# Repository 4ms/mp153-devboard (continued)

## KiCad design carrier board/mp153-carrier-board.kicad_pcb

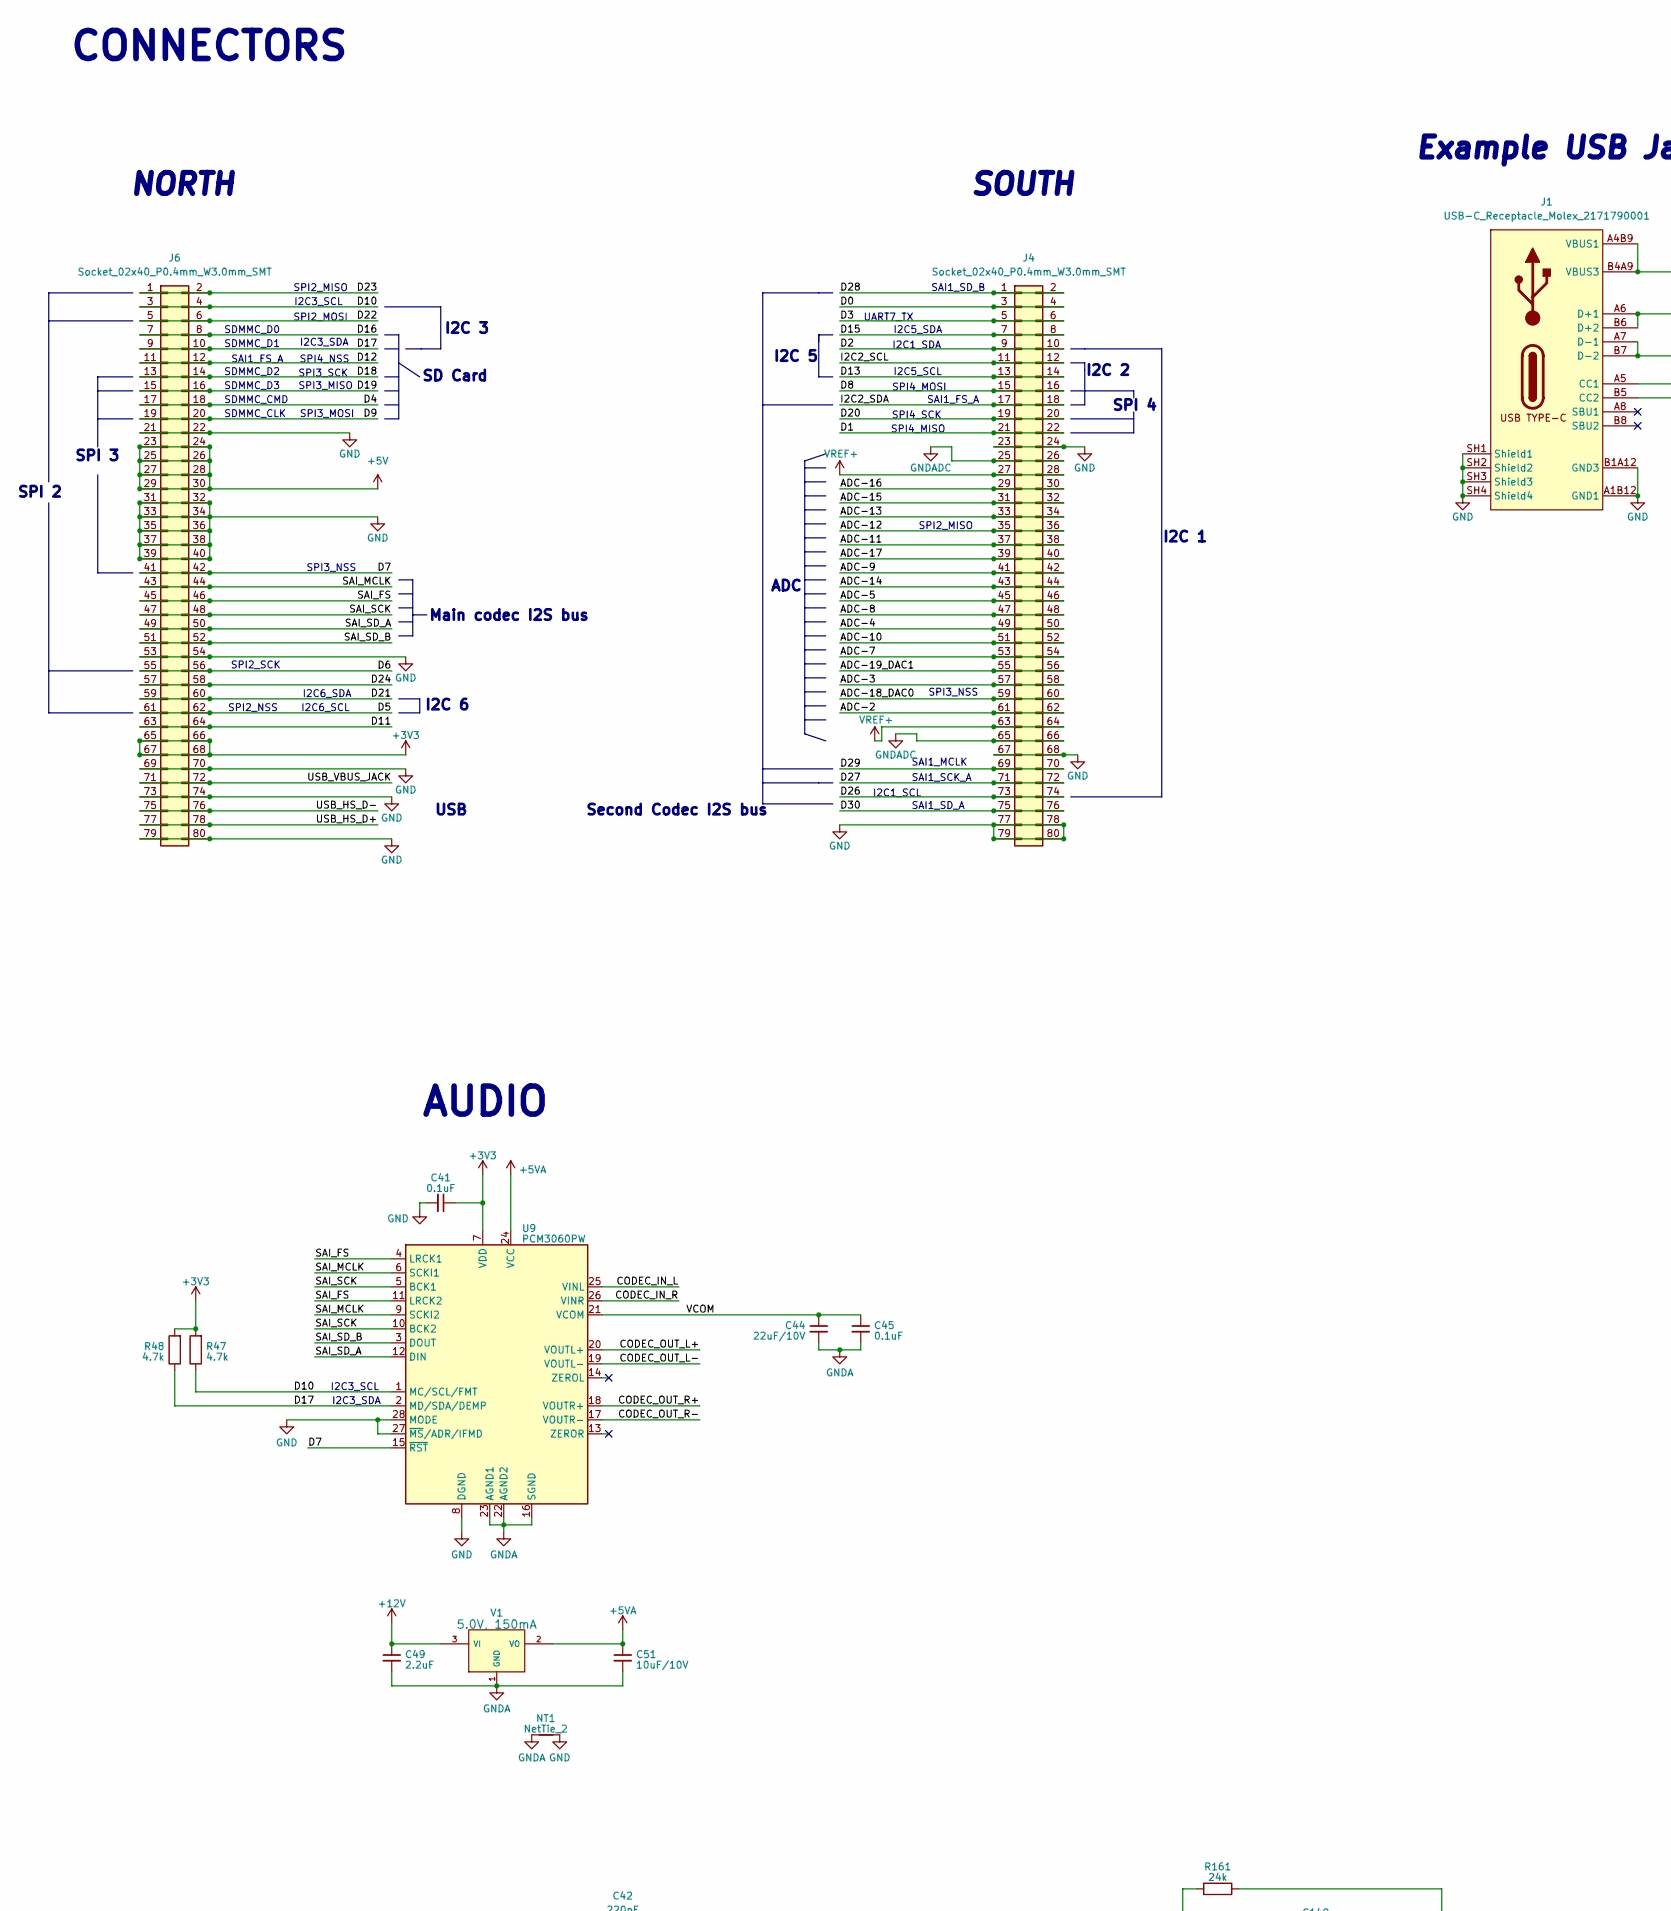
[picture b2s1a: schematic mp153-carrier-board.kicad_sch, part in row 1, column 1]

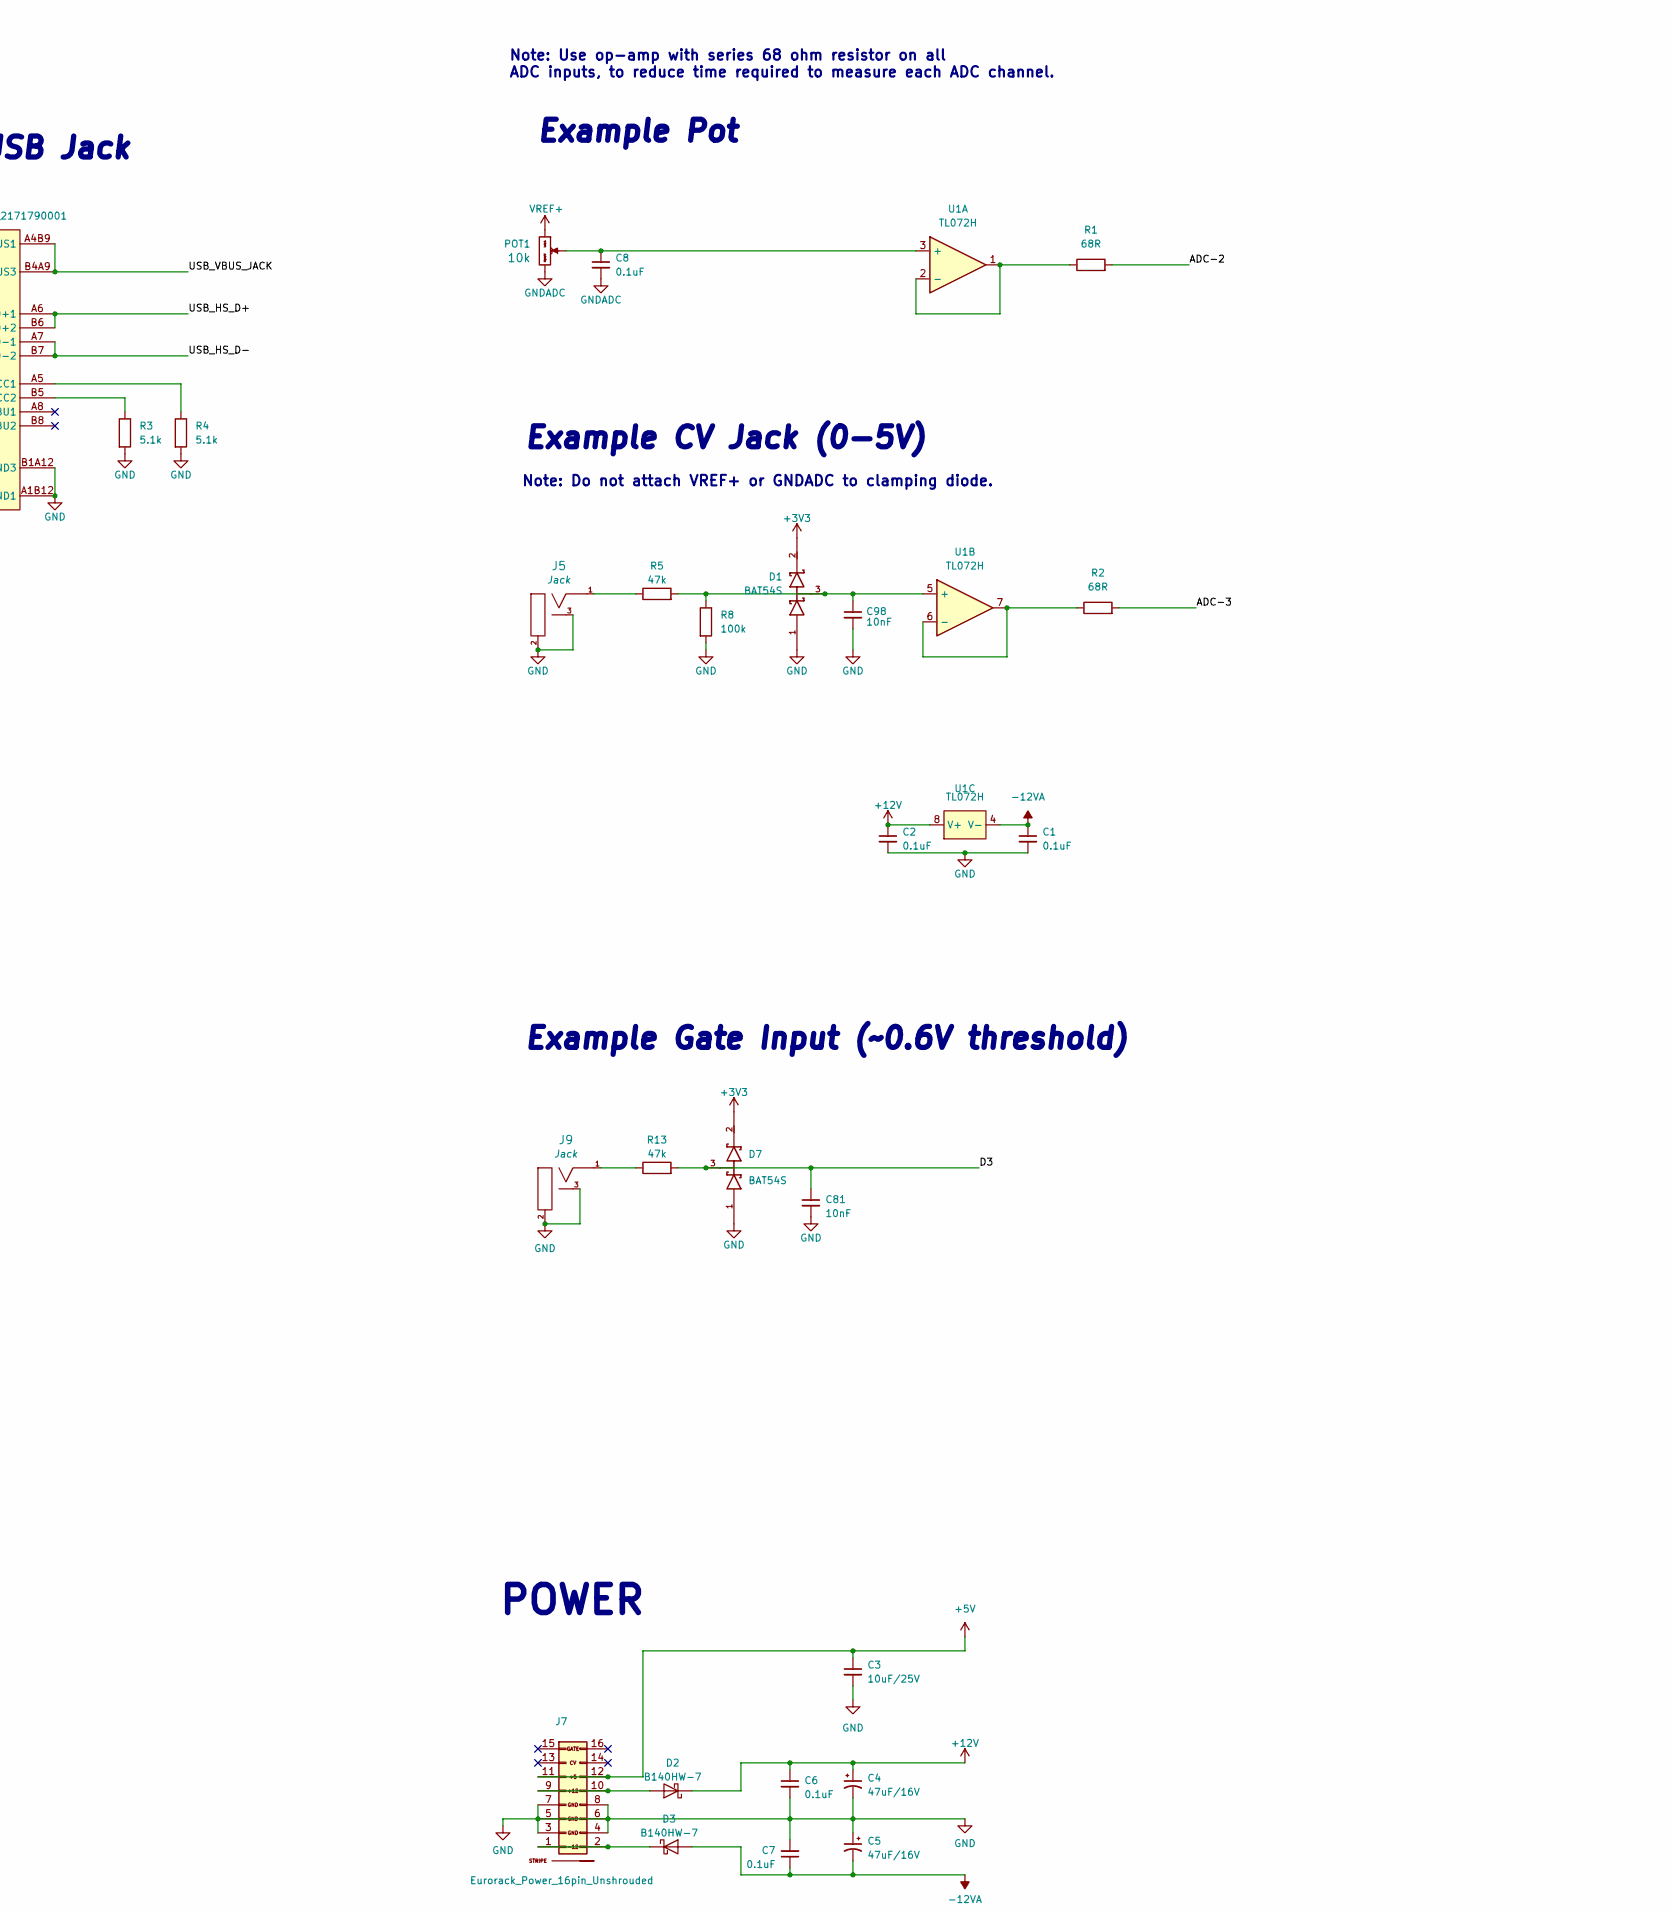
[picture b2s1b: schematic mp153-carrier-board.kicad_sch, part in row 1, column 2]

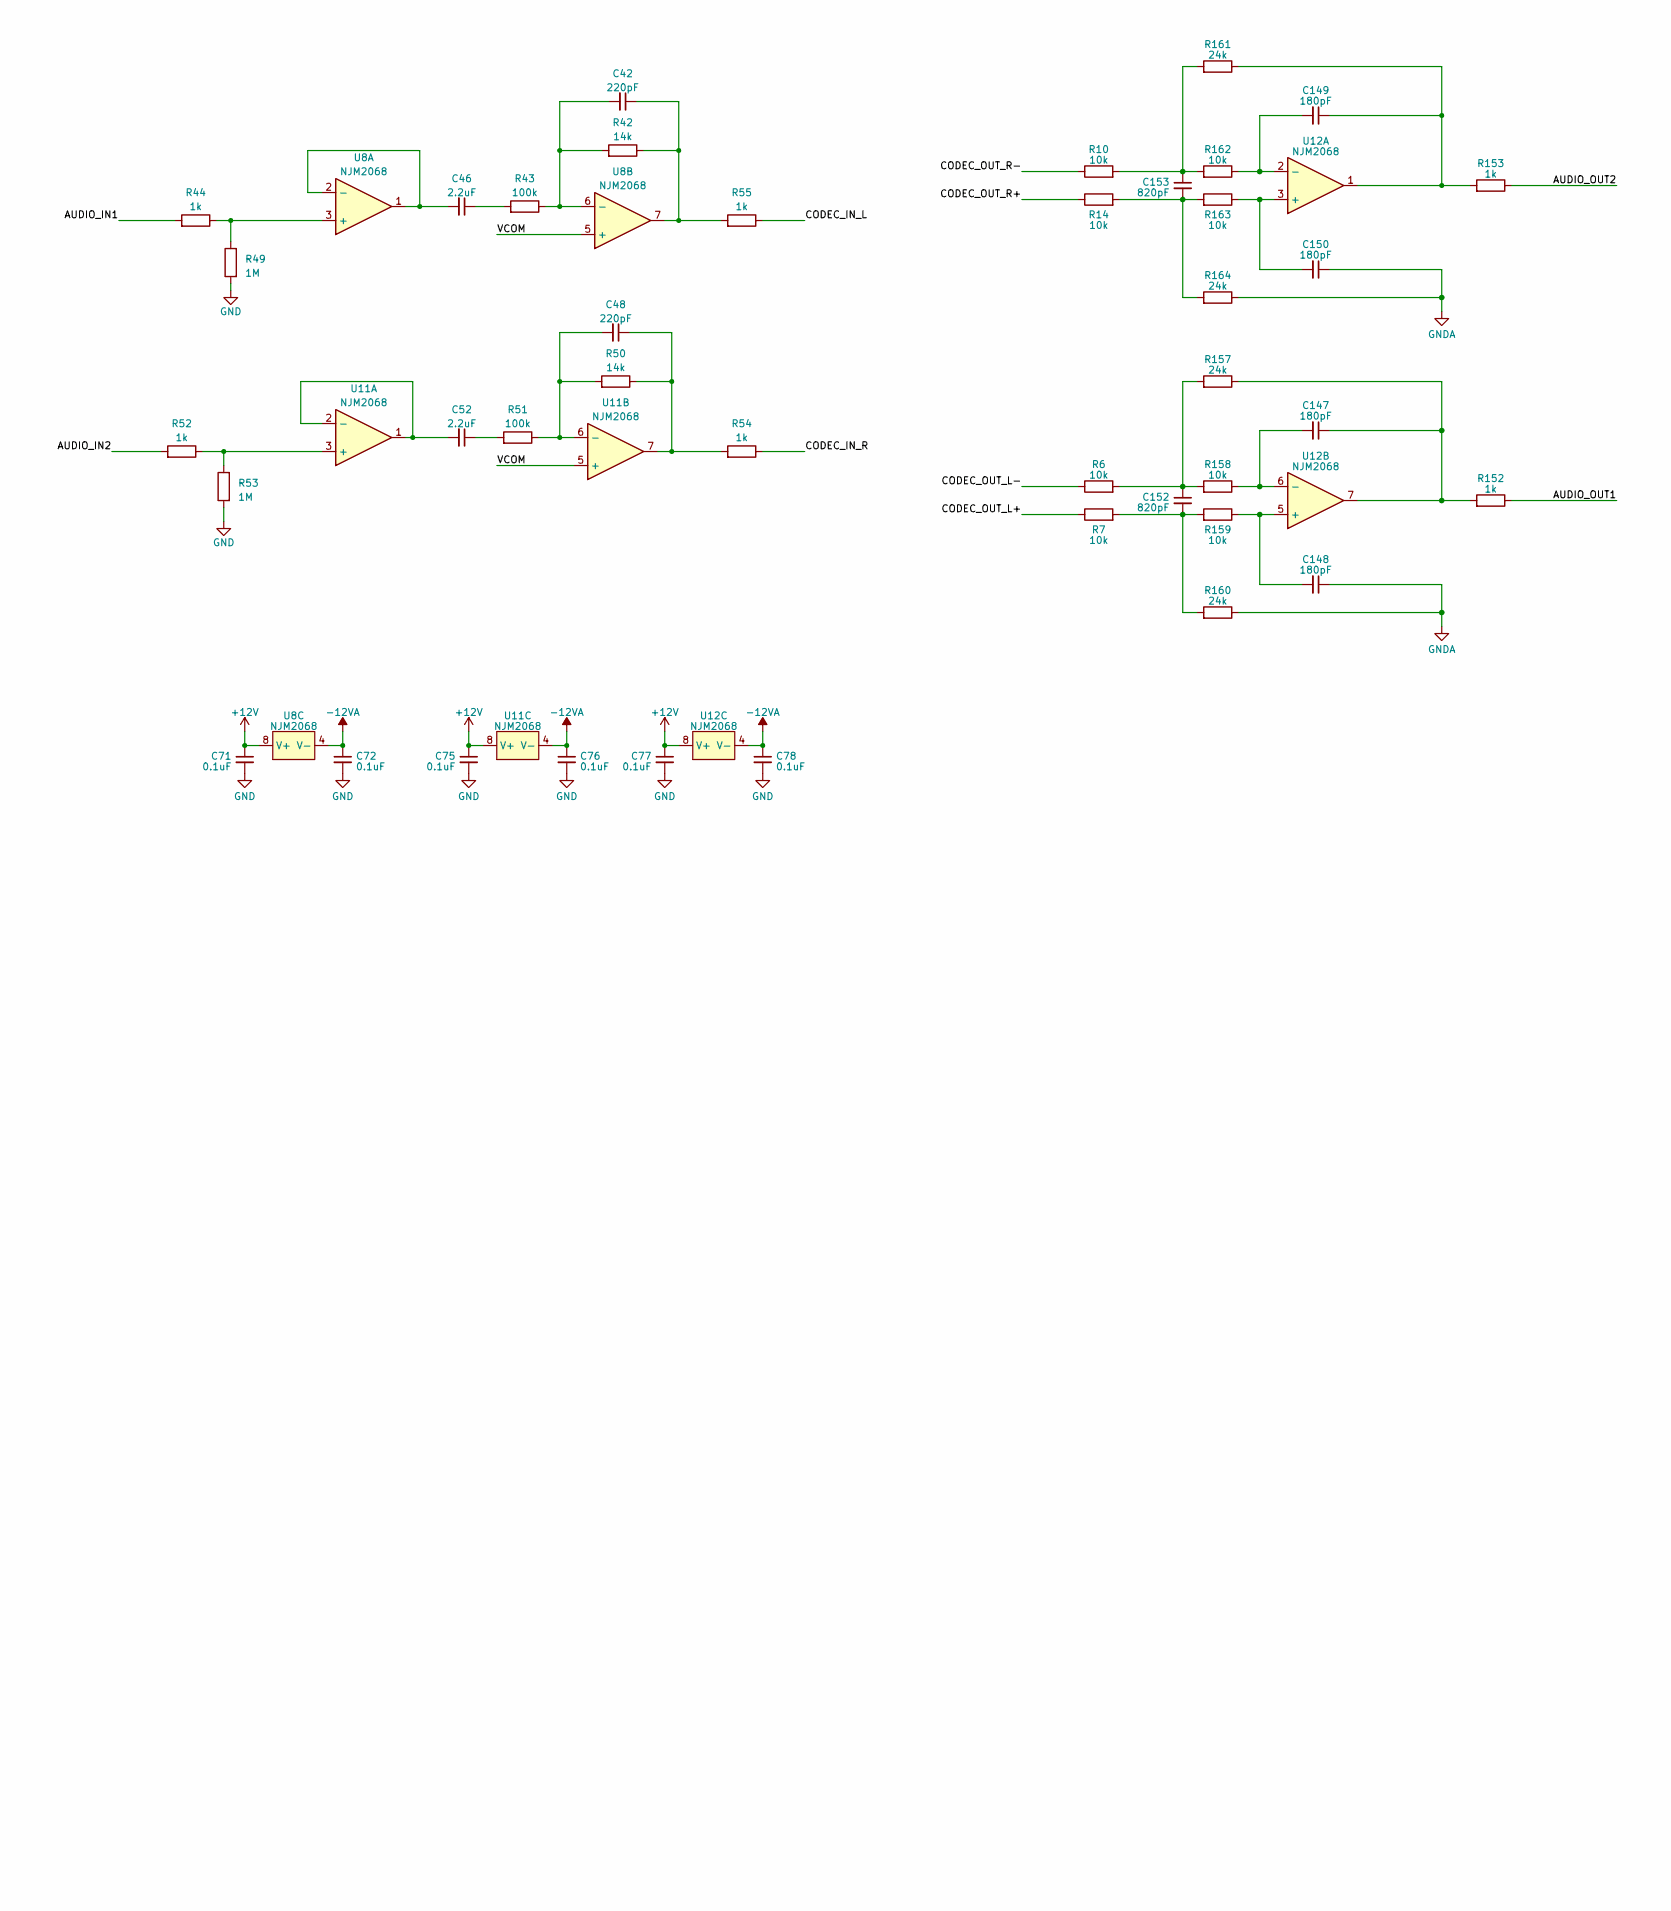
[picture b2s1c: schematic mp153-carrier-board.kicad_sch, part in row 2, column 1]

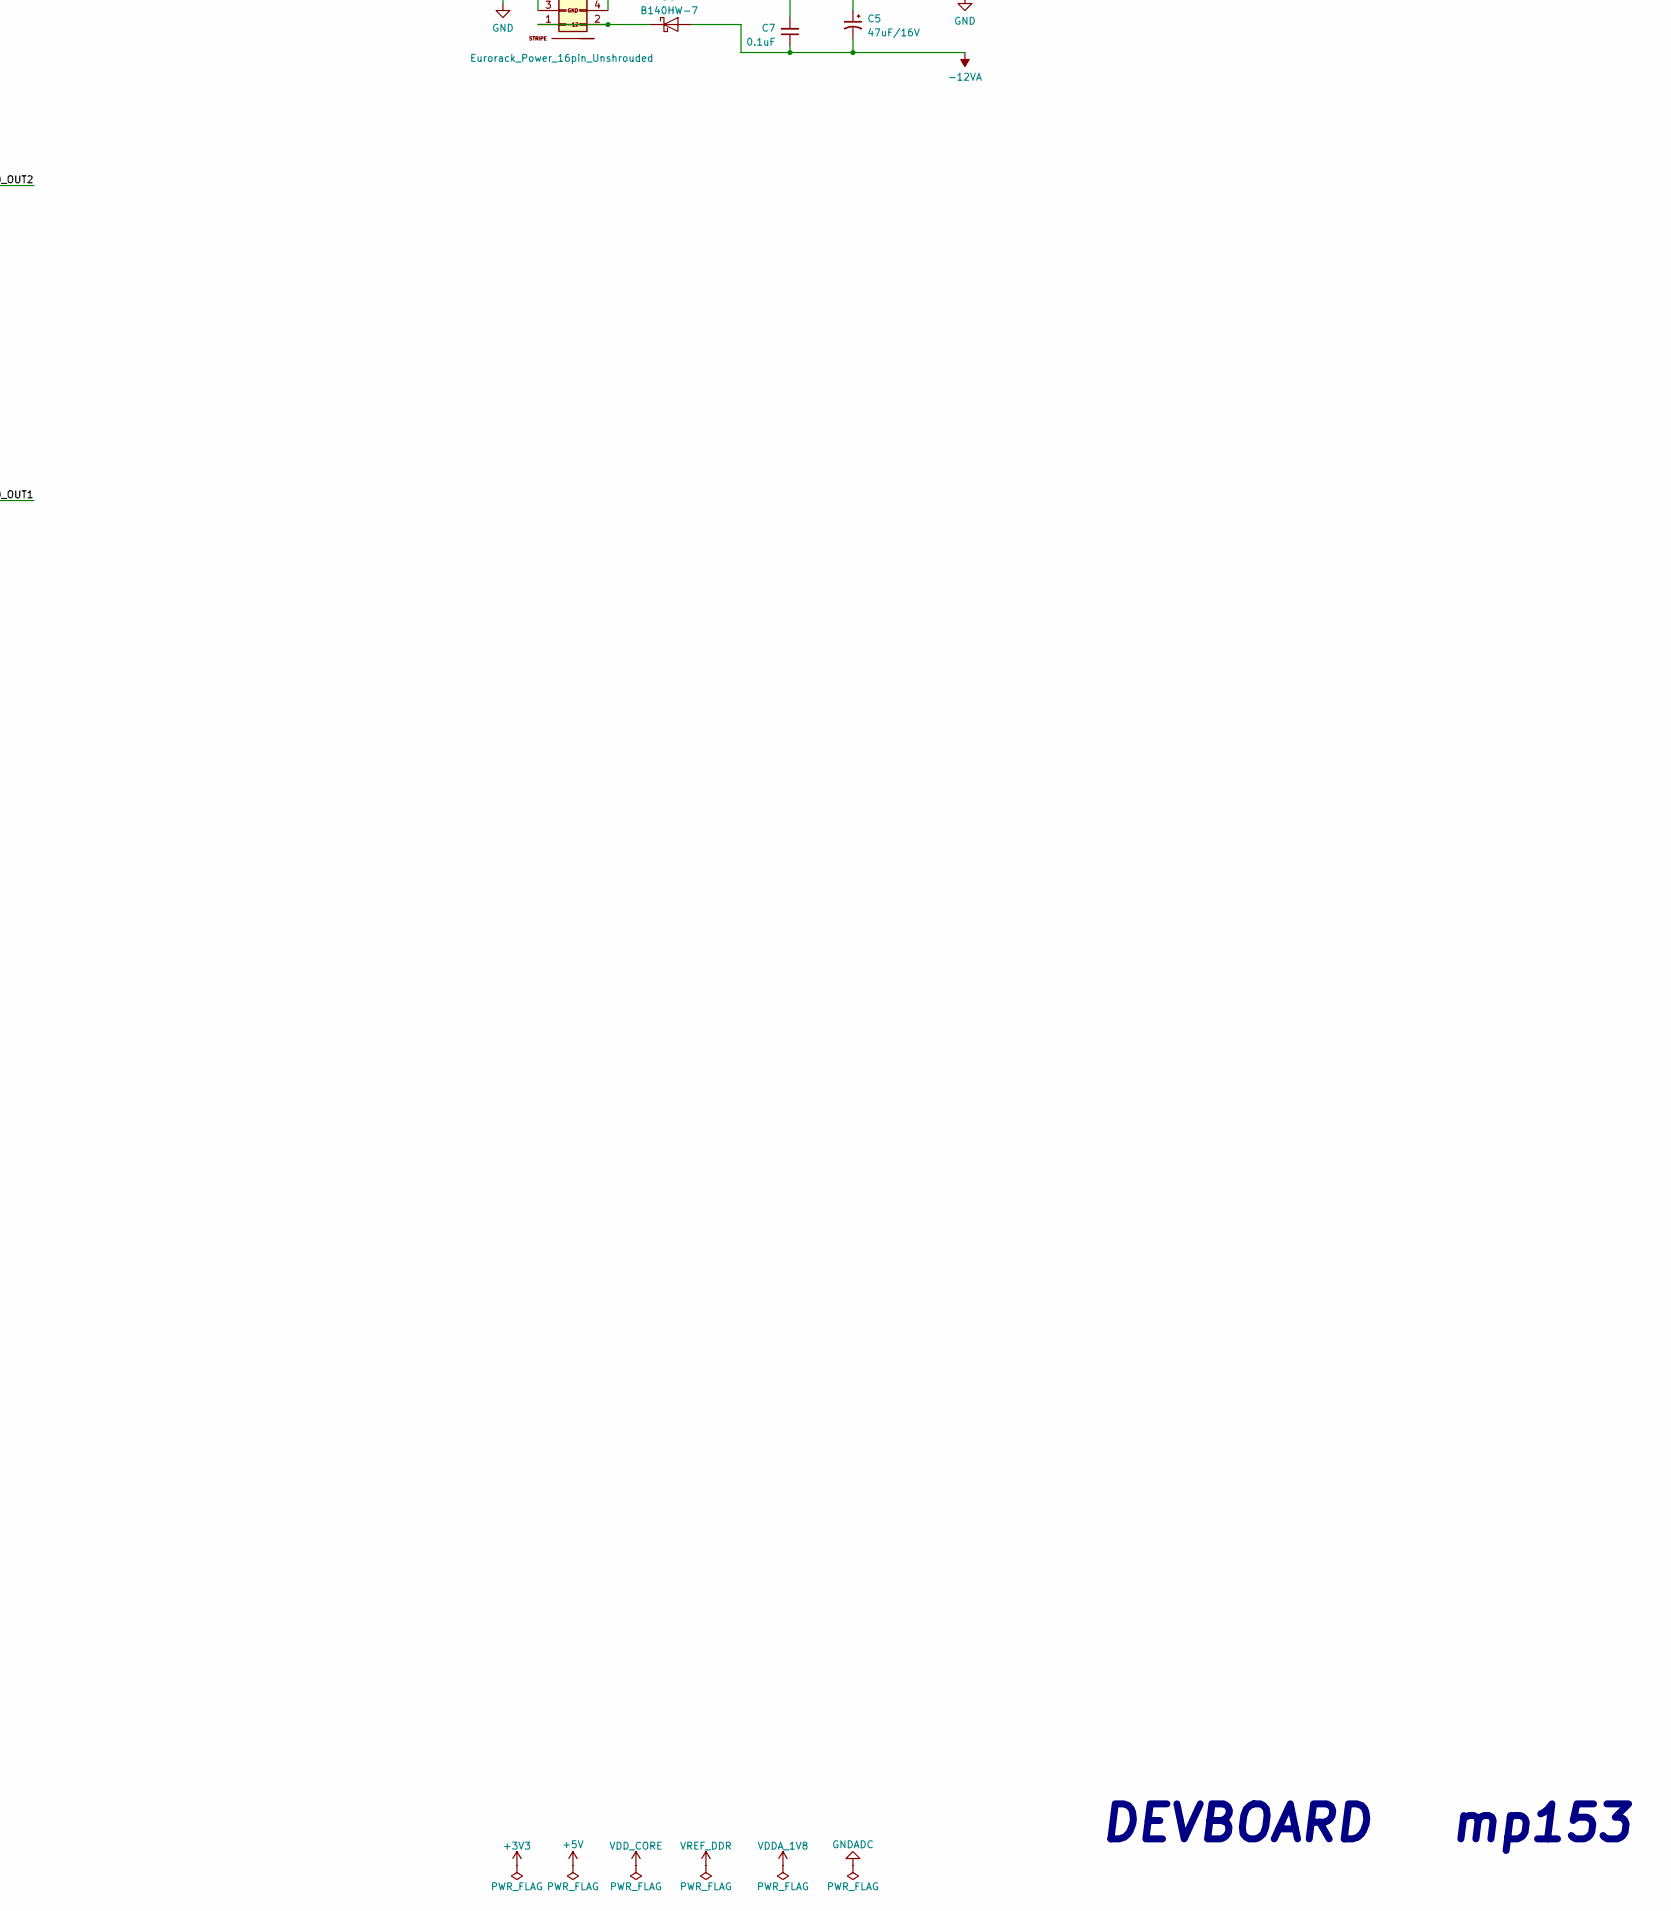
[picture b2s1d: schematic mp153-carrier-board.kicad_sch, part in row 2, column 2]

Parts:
C1, C2, C8: 100nF_0603_16V; C_0603; Part Number 0603YC104KAT2A; JLCPCB ID C14663
C3: 10uF_0805_25V; C_0805; Part Number GRM21BR61E106MA73L; JLCPCB ID C15850
C4, C5: 47uF_5x5.3_16V; CP_Elec_5x5.3; Part Number VES470M1CTR-0505; JLCPCB ID C134798
C6, C7, C41: 100nF_0402_16V; C_0402; Part Number GCM155R71C104KA55D; JLCPCB ID C1525
C42, C48: 220pF_0603_25V; C_0603; Part Number CC0603JRNPO9BN221; JLCPCB ID C1603
C44: 22uF_0805_10V; C_0805; Part Number LMK212BBJ226MG-T; JLCPCB ID C45783
C45: 0.1uF_0603_16V; C_0603; Part Number 0603YC104KAT2A; JLCPCB ID C14663
C46, C49, C52: 2.2uF_0603_25V; C_0603; Part Number GRM188R6YA225KA12D; JLCPCB ID C57895
C51: 10uF_0603_10V; C_0603; Part Number GRM188R61A106KE69D; JLCPCB ID C19702
C71, C72, C75, C76, C77, C78: 100nF_0402_50V; C_0402; Part Number GRM155R71H104KE14D; JLCPCB ID C307331
C81, C98: 10nF_0402_16V; C_0402; Part Number CC0402KRX7R7BB103; JLCPCB ID C15195
C147, C148, C149, C150: 180pF_0402_25V; C_0402; Part Number GRM1555C2A181JE01D; JLCPCB ID C106999
C152, C153: 820pF_0402_10v; C_0402; Part Number 0402ZC821KAT2A; JLCPCB ID C565563
D1, D7: BAT54S; SOT23-3_PO132; Part Number BAT54S-7-F; JLCPCB ID C83574
D2, D3: B140HW-7; D_SOD-123; Part Number B140HW-7; JLCPCB ID C134429
J1: USB-C_Receptacle_Molex_2171790001; USB_C_Receptacle_Molex_2171790001; Part Number 217179-0001; JLCPCB ID C2894899
J4, J6: Socket_02x40_P0.4mm_W3.0mm_SMT; Connector-80socket-P0.4mm-W3.0mm; Part Number DF40HC(3.0)-80DS-0.4V(51); JLCPCB ID C2858577
J5, J9: 3.5mm_Mono_Switched_sm; EighthInch_PJ398SM; Part Number WQP-WQP518MA
J7: Eurorack_Power_16pin_Unshrouded; Pins_2x08_2.54mm_TH_EurorackPower; Part Number 1-1602FBV0T
NT1: NetTie_2; NetTie-2_SMD_Pad0.5mm
POT1: 16mm_CtrDet_10k; Pot_16mm_CtrDet_RV16AF-4A; Part Number RV16AF-4A-15FW-B10k-3C
R1, R2: 68R_0603; R_0603; Part Number RC0603FR-0768RL; JLCPCB ID C27592
R3, R4: 5.1k_0603; R_0603; Part Number RC0603FR-075K1L; JLCPCB ID C105580
R5, R13: 47k_0402; R_0402; Part Number RC0402FR-0747KL; JLCPCB ID C93943
R6, R7, R10, R14, R158, R159, R162, R163: 10k_0402; R_0402; Part Number RC0402FR-0710KL; JLCPCB ID C60490
R8: 100k_0603; R_0603; Part Number RC0603FR-07100KL; JLCPCB ID C14675
R42, R50: 14k_0402; R_0402; Part Number RC0402FR-0714KL; JLCPCB ID C327372
R43, R51: 100k_0402; R_0402; Part Number RC0402FR-07100KL; JLCPCB ID C60491
R44, R52, R54, R55, R152, R153: 1k_0402; R_0402; Part Number RC0402FR-071KL; JLCPCB ID C106235
R47, R48: 4.7k_0402; R_0402; Part Number RC0402FR-074K7L; JLCPCB ID C105871
R49, R53: 1M_0402; R_0402; Part Number RC0402FR-071ML; JLCPCB ID C138033
R157, R160, R161, R164: 24k_0402; R_0402; Part Number RC0402FR-0724KL; JLCPCB ID C138026
U1: TL072H; TSSOP-8_4.4x3mm_Pitch0.65mm; Part Number TL072HIPWR; JLCPCB ID C4370341
U8, U11, U12: NJM2068; TSSOP-8_4.4x3mm_Pitch0.65mm; Part Number NJM2068V-TE1
U9: PCM3060PW; TSSOP-28_4.4x9.7mm_P0.65mm; Part Number PCM3060PW
V1: AP2120N-5.0TRG1; SOT23-3_PO132; Part Number AP2120N-5.0TRG1

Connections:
+3V3: C41.1, D1.2 (cathode), D7.2 (cathode), J6.65, J6.66, J6.67, J6.68, R47.2, R48.2, U9.7 (VDD)
+5V: C3.1, J6.23, J6.24, J6.25, J6.26, J6.27, J6.28, J6.29, J6.30, J7.11 (5V), J7.12 (5V)
+5VA: C51.1, U9.24 (VCC), V1.2 (VO)
+12V: C2.1, C4.1, C6.1, C49.1, C71.1, C75.1, C77.1, D2.1 (K), U1.8 (V+), U8.8 (V+), U11.8 (V+), U12.8 (V+), V1.3 (VI)
-12VA: C1.1, C5.2, C7.1, C72.1, C76.1, C78.1, D3.2 (A), U1.4 (V-), U8.4 (V-), U11.4 (V-), U12.4 (V-)
/ADC-2: J4.61, J4.62, R1.2
/ADC-3: J4.57, J4.58, R2.2
/ADC-4: J4.49, J4.50
/ADC-5: J4.45, J4.46
/ADC-7: J4.53, J4.54
/ADC-8: J4.47, J4.48
/ADC-9: J4.41, J4.42
/ADC-10: J4.51, J4.52
/ADC-11: J4.37, J4.38
/ADC-12: J4.35, J4.36
/ADC-13: J4.33, J4.34
/ADC-14: J4.43, J4.44
/ADC-15: J4.31, J4.32
/ADC-16: J4.29, J4.30
/ADC-17: J4.39, J4.40
/ADC-18_DAC0: J4.59, J4.60
/ADC-19_DAC1: J4.55, J4.56
/AUDIO_IN1: R44.2
/AUDIO_IN2: R52.2
/AUDIO_OUT1: R152.1
/AUDIO_OUT2: R153.1
/CODEC_IN_L: R55.1, U9.25 (VINL)
/CODEC_IN_R: R54.1, U9.26 (VINR)
/CODEC_OUT_L+: R7.1, U9.20 (VOUTL+)
/CODEC_OUT_L-: R6.1, U9.19 (VOUTL-)
/CODEC_OUT_R+: R14.1, U9.18 (VOUTR+)
/CODEC_OUT_R-: R10.1, U9.17 (VOUTR-)
/D0: J4.3, J4.4
/D1: J4.21, J4.22
/D2: J4.9, J4.10
/D3: C81.1, D7.3 (AK), J4.5, J4.6, R13.2
/D4: J6.17, J6.18
/D5: J6.61, J6.62
/D6: J6.55, J6.56
/D7: J6.41, J6.42, U9.15 (~RST)
/D8: J4.15, J4.16
/D9: J6.19, J6.20
/D10: J6.3, J6.4, R47.1, U9.1 (MC/SCL/FMT)
/D11: J6.63, J6.64
/D12: J6.11, J6.12
/D13: J4.13, J4.14
/D15: J4.7, J4.8
/D16: J6.7, J6.8
/D17: J6.9, J6.10, R48.1, U9.2 (MD/SDA/DEMP)
/D18: J6.13, J6.14
/D19: J6.15, J6.16
/D20: J4.19, J4.20
/D21: J6.59, J6.60
/D22: J6.5, J6.6
/D23: J6.1, J6.2
/D24: J6.57, J6.58
/D26: J4.73, J4.74
/D27: J4.71, J4.72
/D28: J4.1, J4.2
/D29: J4.69, J4.70
/D30: J4.75, J4.76
/I2C2_SCL: J4.11, J4.12
/I2C2_SDA: J4.17, J4.18
/SAI_FS: J6.45, J6.46, U9.4 (LRCK1), U9.11 (LRCK2)
/SAI_MCLK: J6.43, J6.44, U9.6 (SCKI1), U9.9 (SCKI2)
/SAI_SCK: J6.47, J6.48, U9.5 (BCK1), U9.10 (BCK2)
/SAI_SD_A: J6.49, J6.50, U9.12 (DIN)
/SAI_SD_B: J6.51, J6.52, U9.3 (DOUT)
/USB_HS_D+: J1.A6 (D+1), J1.B6 (D+2), J6.77, J6.78
/USB_HS_D-: J1.A7 (D-1), J1.B7 (D-2), J6.75, J6.76
/USB_VBUS_JACK: J1.A4B9 (VBUS1), J1.B4A9 (VBUS3), J6.71, J6.72
/VCOM: C44.1, C45.1, U8.5 (+), U9.21 (VCOM), U11.5 (+)
GND: C1.2, C2.2, C3.2, C4.2, C5.1, C6.2, C7.2, C41.2, C71.2, C72.2, C75.2, C76.2, C77.2, C78.2, C81.2, C98.2, D1.1 (Anode), D7.1 (Anode), J1.A1B12 (GND1), J1.B1A12 (GND3), J1.SH1 (Shield1), J1.SH2 (Shield2), J1.SH3 (Shield3), J1.SH4 (Shield4), J4.23, J4.24, J4.67, J4.68, J4.77, J4.78, J4.79, J4.80, J5.2 (SHEILD), J5.3 (SW), J6.21, J6.22, J6.31, J6.32, J6.33, J6.34, J6.35, J6.36, J6.37, J6.38, J6.39, J6.40, J6.53, J6.54, J6.69, J6.70, J6.73, J6.74, J6.79, J6.80, J7.3 (GND), J7.4 (GND), J7.5 (GND), J7.6 (GND), J7.7 (GND), J7.8 (GND), J9.2 (SHEILD), J9.3 (SW), NT1.2, R3.2, R4.2, R8.2, R49.2, R53.2, U9.8 (DGND), U9.27 (~MS/ADR/IFMD), U9.28 (MODE)
GNDA: C44.2, C45.2, C49.2, C51.2, C148.1, C150.1, NT1.1, R160.1, R164.1, U9.16 (SGND), U9.22 (AGND2), U9.23 (AGND1), V1.1 (GND)
GNDADC: C8.2, J4.25, J4.26, J4.65, J4.66, POT1.3 (Right)
unnamed: C42.1, R42.1, R55.2, U8.7
unnamed: C46.1, R43.2
unnamed: C48.1, R50.1, R54.2, U11.7
unnamed: C52.1, R51.2
unnamed: C147.1, R152.2, R157.1, U12.7
unnamed: C149.1, R153.2, R161.1, U12.1
unnamed: C152.1, R6.2, R157.2, R158.2
unnamed: C152.2, R7.2, R159.2, R160.2
unnamed: C153.1, R10.2, R161.2, R162.2
unnamed: C153.2, R14.2, R163.2, R164.2
unnamed: C98.1, D1.3 (AK), R5.2, R8.1, U1.5 (+)
unnamed: D2.2 (A), J7.9 (+12V), J7.10 (+12V)
unnamed: D3.1 (K), J7.1 (-12V), J7.2 (-12V)
unnamed: J1.A5 (CC1), R4.1
unnamed: J1.B5 (CC2), R3.1
unnamed: J5.1 (SIG), R5.1
unnamed: J9.1 (SIG), R13.1
unnamed: C8.1, POT1.2 (Center), U1.3 (+)
unnamed: R1.1, U1.1, U1.2 (-)
unnamed: R2.1, U1.6 (-), U1.7
unnamed: R44.1, R49.1, U8.3 (+)
unnamed: C46.2, U8.1, U8.2 (-)
unnamed: C42.2, R42.2, R43.1, U8.6 (-)
unnamed: R52.1, R53.1, U11.3 (+)
unnamed: C52.2, U11.1, U11.2 (-)
unnamed: C48.2, R50.2, R51.1, U11.6 (-)
unnamed: C150.2, R163.1, U12.3 (+)
unnamed: C149.2, R162.1, U12.2 (-)
unnamed: C148.2, R159.1, U12.5 (+)
unnamed: C147.2, R158.1, U12.6 (-)
VREF+: J4.27, J4.28, J4.63, J4.64, POT1.1 (Left)

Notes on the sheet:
SDMMC_CMD
UART7_TX
SPI2_MISO
I2C 5
SPI3_NSS
Example CV Jack (0-5V)
SPI3_MISO
SPI3_SCK
SPI 3
I2C 6
POWER
I2C 3
SPI 4
Second Codec I2S bus
I2C6_SDA
Main codec I2S bus
SPI 2
I2C3_SCL
mp153
SD Card
SDMMC_D3
I2C1_SDA
I2C3_SDA
CONNECTORS
SAI1_SD_A
I2C5_SCL
SAI1_SD_B
SDMMC_CLK
Note: Use op-amp with series 68 ohm resistor on all ADC inputs, to reduce time required to measure each ADC channel.
Example Gate Input (~0.6V threshold)
I2C 2
SPI4_SCK
SPI2_MOSI
SAI1_FS_A
SPI4_MISO
SOUTH
NORTH
Example USB Jack
Note: Do not attach VREF+ or GNDADC to clamping diode.
SPI4_NSS

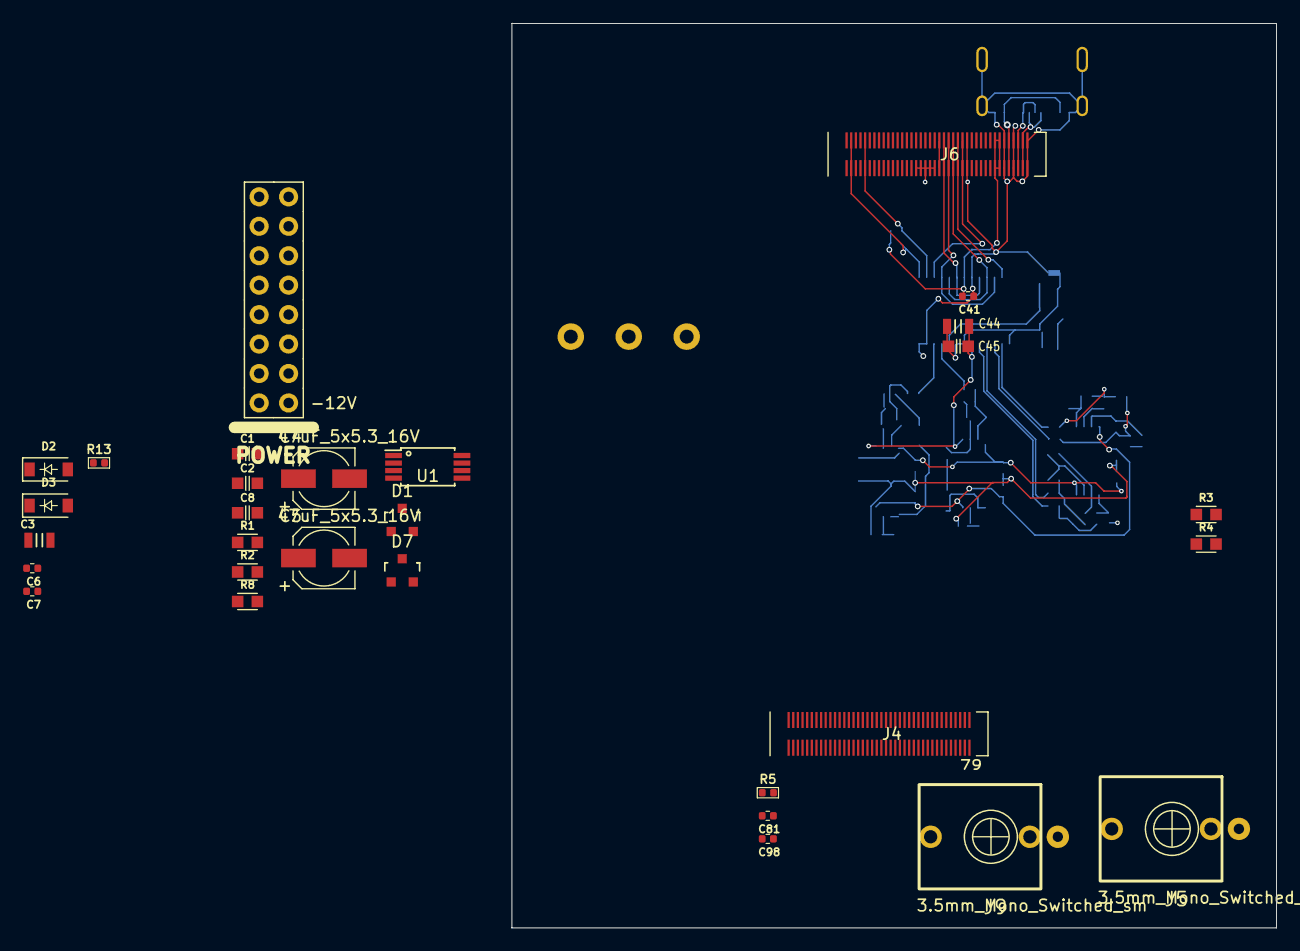
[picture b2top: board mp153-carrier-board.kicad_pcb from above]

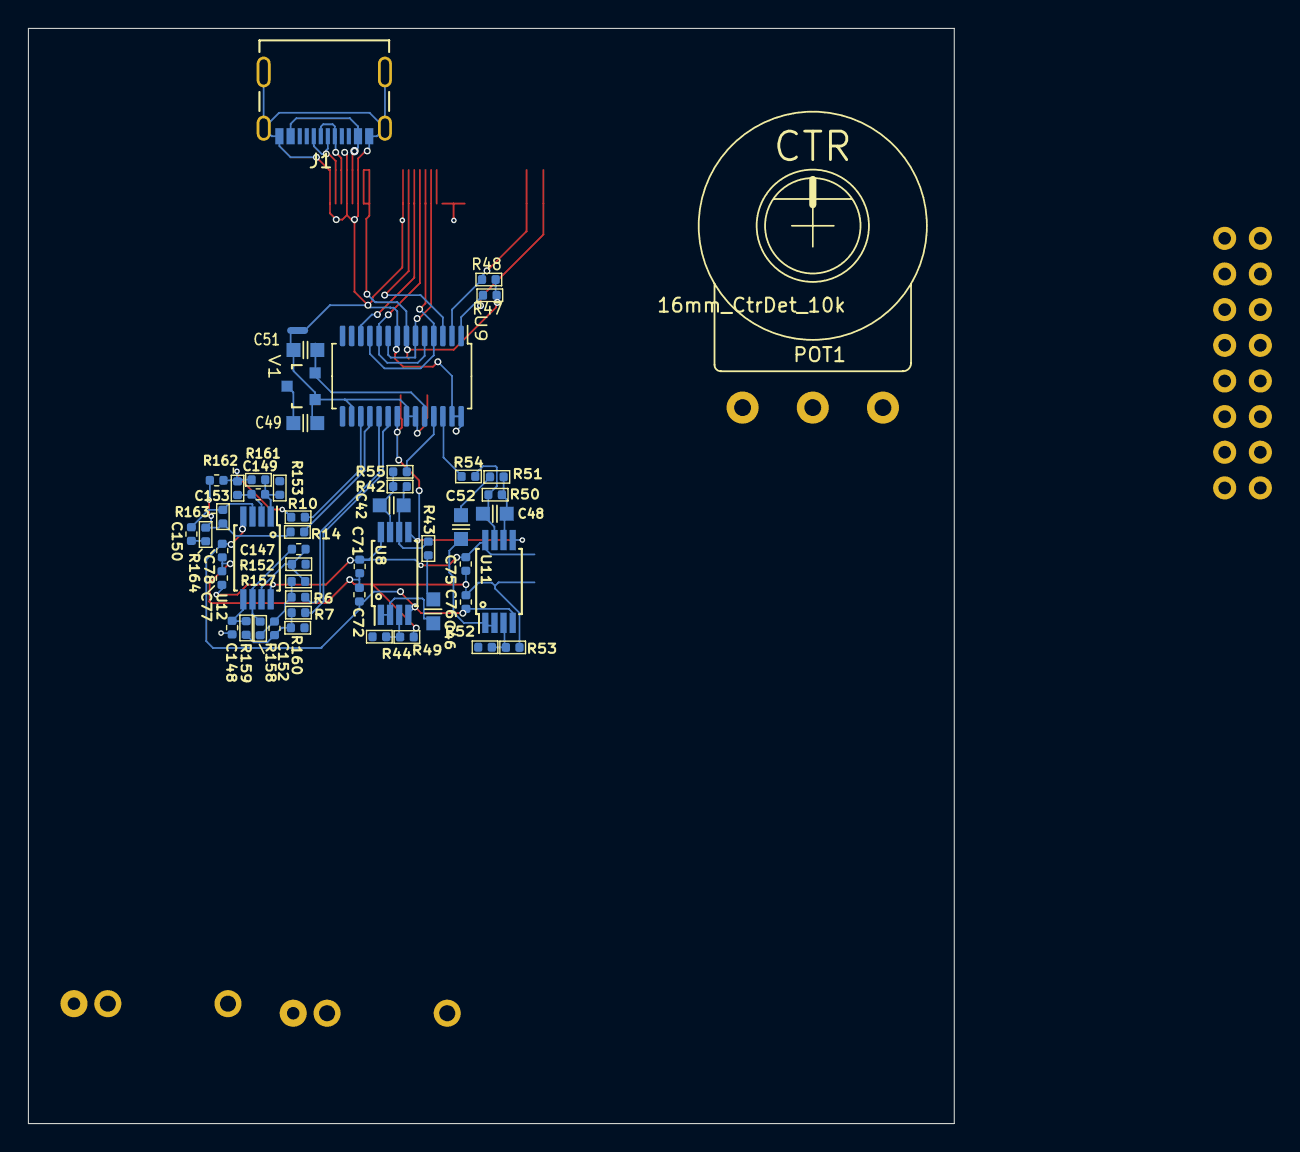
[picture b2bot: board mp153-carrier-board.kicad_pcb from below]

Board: 4 copper layers, 66.0 x 78.0 mm, 82 parts (52 on the bottom side), 102 nets.

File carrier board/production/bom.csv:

Designator,Footprint,Quantity,Value,LCSC Part #
"C1, C2, C6, C7, C8",C_0603,5,100nF_0603_16V,C14663
"C147, C148, C149, C150",C_0402,4,180pF_0402_25V,C106999
"C152, C153",C_0402,2,820pF_0402_10v,C565563
C3,C_0805,1,10uF_0805_25V,C15850
"C4, C5",CP_Elec_5x5.3,2,47uF_5x5.3_16V,C134798
"C41, C45",C_0402,2,100nF_0402_16V,C1525
"C42, C48",C_0603,2,220pF_0603_25V,C1603
C44,C_0805,1,22uF_0805_25V,C45783
"C46, C49, C52",C_0603,3,2.2uF_0603_25V,C57895
C51,C_0603,1,10uF_0603_10V,C19702
"C71, C72, C75, C76, C77, C78",C_0402,6,100nF_0402_50V,C307331
"C81, C98",C_0603,2,10nF_0603_25V,C57112
"D1, D7",SOT23-3_PO132,2,BAT54S,C83574
"D2, D3",D_SOD-123,2,B140HW-7,C134429
J1,USB_C_Receptacle_Molex_2171790001,1,USB-C_Receptacle_Molex_2171790001,C2894899
"J10, J11, J12, J13, J5, J9",EighthInch_PJ398SM,6,3.5mm_Mono_Switched_sm,
"J4, J6",Connector-80socket-P0.4mm-W3.0mm,2,Socket_02x40_P0.4mm_W3.0mm_SMT,C2858577
J7,Pins_2x08_2.54mm_TH_EurorackPower,1,Eurorack_Power_16pin_Unshrouded,
POT1,Pot_9mm_Knurl_NoDet,1,9mm_NoDet_100k_Knurled_Lined,
"R1, R2",R_0603,2,68Ω_0603,C126362
"R10, R14, R158, R159, R162, R163, R6, R7",R_0402,8,10k_0402,C60490
"R13, R5",R_0603,2,47k_0603,C105579
"R152, R153, R44, R52, R54, R55",R_0402,6,1k_0402,C106235
"R157, R160, R161, R164",R_0402,4,24k_0402,C138026
"R3, R4",R_0603,2,5.1k_0603,C105580
"R42, R50",R_0402,2,14k_0402,C327372
"R43, R51",R_0402,2,100k_0402,C60491
"R47, R48",R_0402,2,4.7k_0402,C105871
"R49, R53",R_0402,2,1M_0402,C138033
R8,R_0603,1,100k_0603,C14675
"U1, U11, U12, U8",TSSOP-8_4.4x3mm_Pitch0.65mm,4,TL072H,C4370341
U9,TSSOP-28_4.4x9.7mm_P0.65mm,1,PCM3060PW,C2651841
V1,SOT23-3_PO132,1,AP2120N-5.0TRG1,C50754
